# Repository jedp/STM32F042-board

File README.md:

## STM32F042 Board

Dev board for the
[STM32F042](https://www.st.com/resource/en/datasheet/stm32f042c4.pdf).

### Programming

I'm using the ST-Link on an ST Discovery board to program this.

These ST Header CN2 Pins should be connected to the corresponding pins on this
dev board:

1. Don't connect
2. CLK
3. GND
4. DIO
5. NRST

Leave pin 1 (target 3V3) unconnected. It seems to do no harm, but it won't work
if connected.

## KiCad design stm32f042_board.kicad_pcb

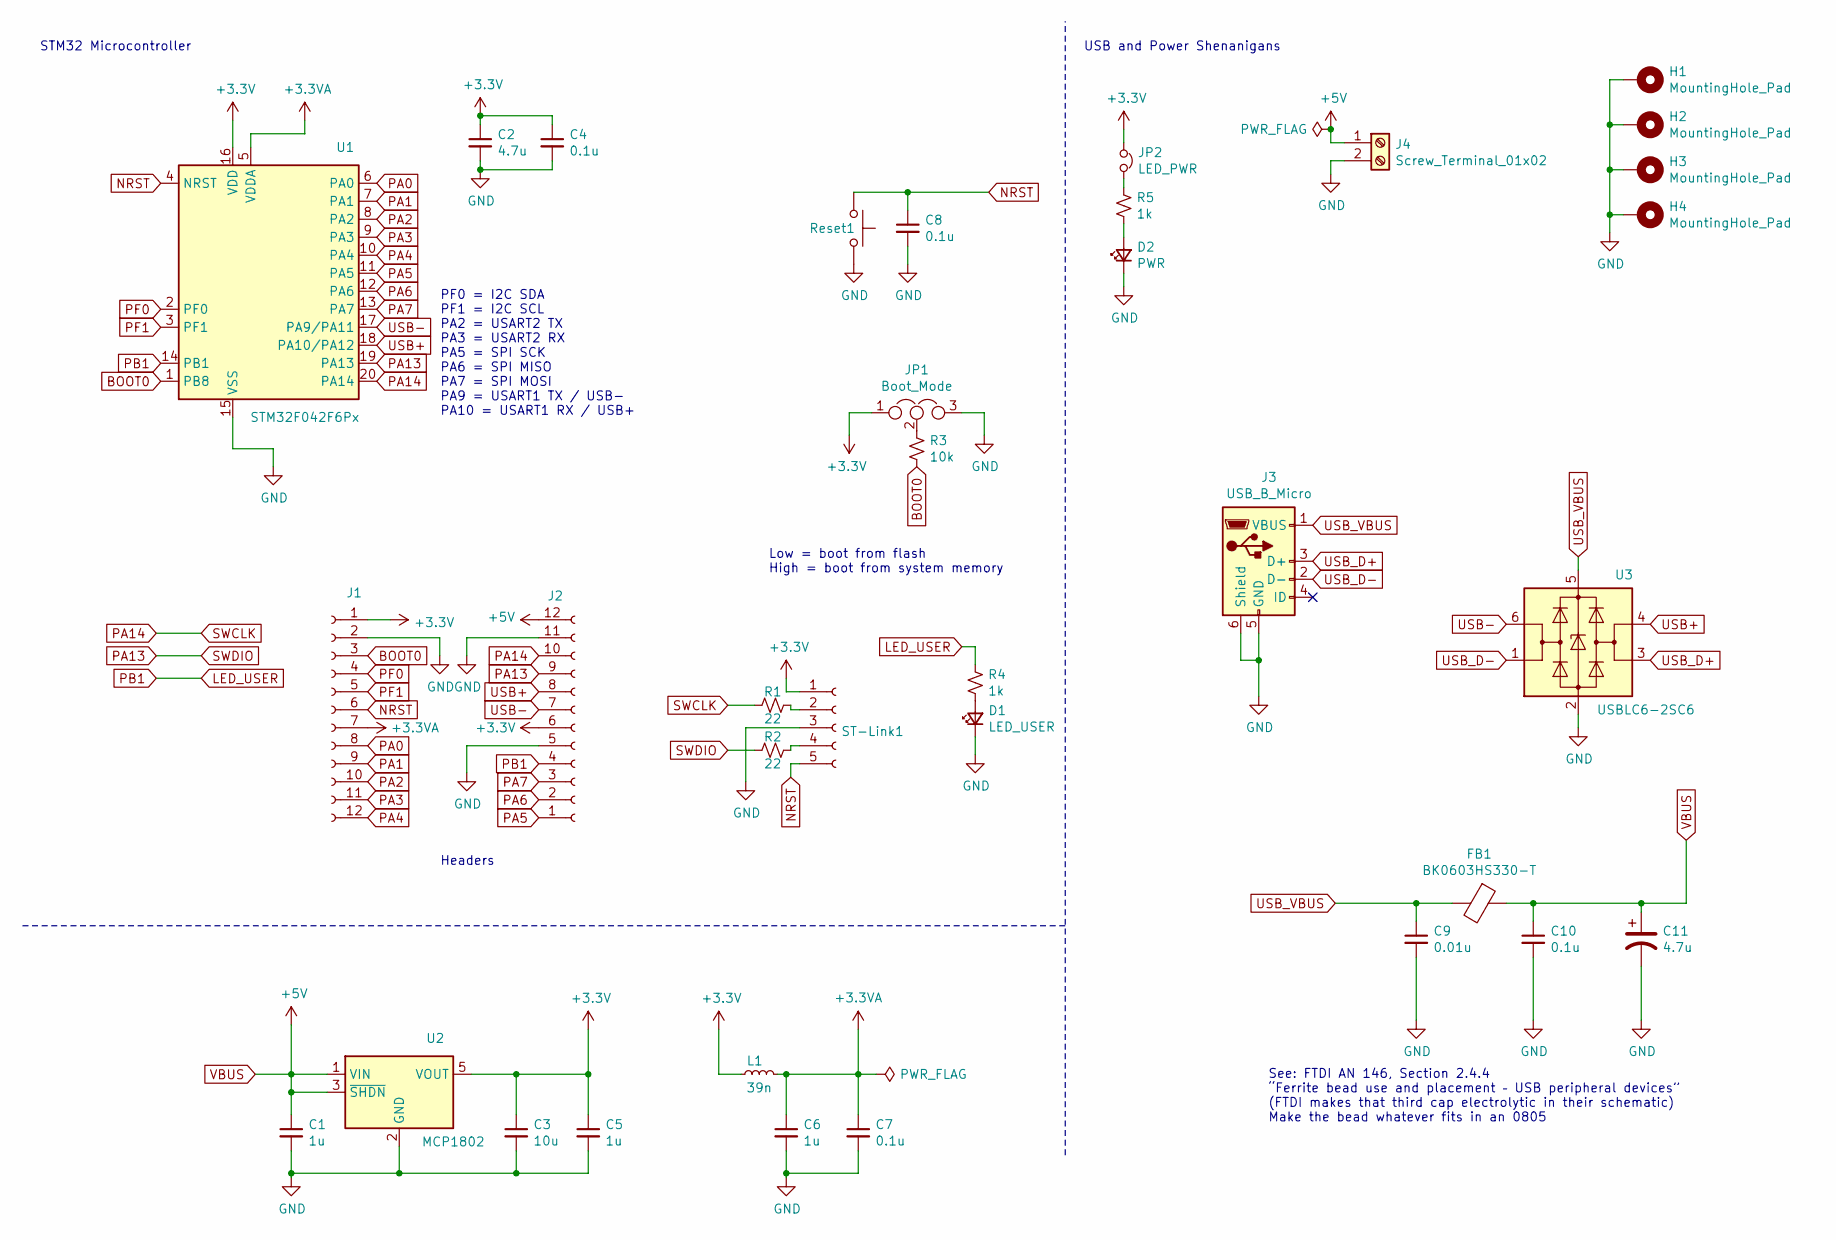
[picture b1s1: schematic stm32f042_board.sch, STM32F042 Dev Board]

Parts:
C1, C5: 1u; C_0805_2012Metric
C2: 4.7u; C_0603_1608Metric
C3: 10u; C_0805_2012Metric
C4, C7: 0.1u; C_0603_1608Metric
C6: 1u; C_0603_1608Metric
C8, C10: 0.1u; C_0805_2012Metric
C9: 0.01u; C_0805_2012Metric
C11: 4.7u; CP_Elec_4x5.4
D1: LED_USER; LED_0603_1608Metric
D2: PWR; LED_0603_1608Metric
FB1: BK0603HS330-T; L_0805_2012Metric
H1, H2, H3, H4: MountingHole_Pad; MountingHole_3.2mm_M3_ISO7380_Pad
J1, J2: Conn_01x12_Female; PinSocket_1x12_P2.54mm_Vertical
J3: USB_B_Micro; USB_Micro-B_Molex-105017-0001
J4: Screw_Terminal_01x02; TerminalBlock_MetzConnect_Type055_RT01502HDWU_1x02_P5.00mm_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
JP1: Boot_Mode; PinHeader_1x03_P2.54mm_Vertical
JP2: LED_PWR; PinHeader_1x02_P2.54mm_Vertical
L1: 39n; L_0805_2012Metric
R1, R2: 22; R_0805_2012Metric
R3: 10k; R_0603_1608Metric
R4, R5: 1k; R_0805_2012Metric
Reset1: SW_Push; SW_SPST_B3U-1000P-B
ST-Link1: Conn_01x05_Female; PinHeader_1x05_P2.54mm_Vertical
U1: STM32F042F6Px; TSSOP-20_4.4x6.5mm_P0.65mm
U2: MCP1802; SOT-23-5
U3: USBLC6-2SC6; SOT-23-6

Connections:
+3.3VA: C6.1, C7.1, J1.7, L1.2, U1.5 (VDDA)
+3V3: C2.1, C3.1, C4.1, C5.1, J1.1, J2.6, JP1.1, JP2.1, L1.1, ST-Link1.1, U1.16 (VDD), U2.5 (VOUT); also elsewhere on the board
BOOT0: J1.3, R3.2, U1.1 (PB8)
GND: C1.2, C2.2, C3.2, C4.2, C5.2, C6.2, C7.2, C8.2, C9.2, C10.2, C11.2, D1.1 (K), D2.1 (K), H1.1, H2.1, H3.1, H4.1, J1.2, J2.5, J2.11, J3.5 (GND), J3.6 (Shield), J4.2, JP1.3, Reset1.2, ST-Link1.3, U1.15 (VSS), U2.2 (GND), U3.2 (GND); also elsewhere on the board
LED_USER: J2.4, R4.1, U1.14 (PB1)
NRST: C8.1, J1.6, Reset1.1, ST-Link1.5, U1.4 (NRST); also elsewhere on the board
unnamed 6: D1.2 (A), R4.2; also elsewhere on the board
unnamed: D2.2 (A), R5.2
unnamed: JP1.2, R3.1
unnamed: JP2.2, R5.1
unnamed 11: R1.1, ST-Link1.2; also elsewhere on the board
unnamed 12: R2.1, ST-Link1.4; also elsewhere on the board
PA0: J1.8, U1.6 (PA0)
PA1: J1.9, U1.7 (PA1)
PA2: J1.10, U1.8 (PA2)
PA3: J1.11, U1.9 (PA3)
PA4: J1.12, U1.10 (PA4)
PA5: J2.1, U1.11 (PA5)
PA6: J2.2, U1.12 (PA6)
PA7: J2.3, U1.13 (PA7)
PA13: J2.9, R2.2, U1.19 (PA13)
PA14: J2.10, R1.2, U1.20 (PA14)
PF0: J1.4, U1.2 (PF0)
PF1: J1.5, U1.3 (PF1)
USB+: J2.8, U1.18 (PA10/PA12), U3.4 (I/O2)
USB-: J2.7, U1.17 (PA9/PA11), U3.6 (I/O1)
USB_D+: J3.3 (D+), U3.3 (I/O2)
USB_D-: J3.2 (D-), U3.1 (I/O1)
USB_VBUS: C9.1, FB1.2, J3.1 (VBUS), U3.5 (VBUS)
VBUS: C1.1, C10.1, C11.1, FB1.1, J2.12, J4.1, U2.1 (VIN), U2.3 (~SHDN)

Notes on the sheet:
Low = boot from flash High = boot from system memory
See: FTDI AN 146, Section 2.4.4 “Ferrite bead use and placement – USB peripheral devices” (FTDI makes that third cap electrolytic in their schematic) Make the bead whatever fits in an 0805
STM32 Microcontroller
Headers
PF0 = I2C SDA PF1 = I2C SCL PA2 = USART2 TX PA3 = USART2 RX PA5 = SPI SCK PA6 = SPI MISO PA7 = SPI MOSI PA9 = USART1 TX / USB- PA10 = USART1 RX / USB+
USB and Power Shenanigans

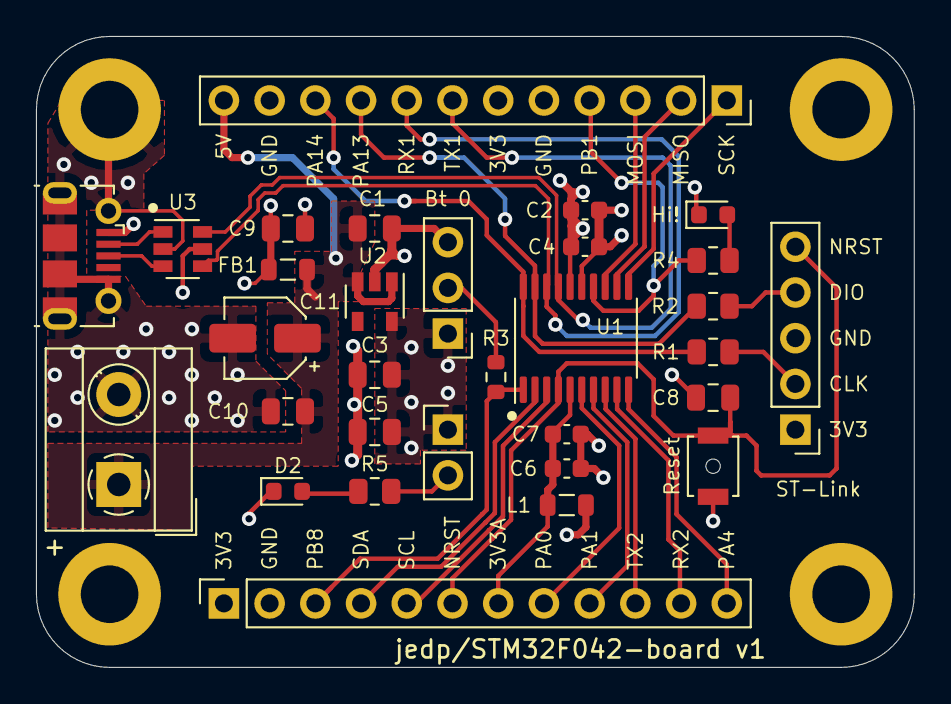
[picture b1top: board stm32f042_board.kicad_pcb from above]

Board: 4 copper layers, 48.8 x 35.1 mm, 35 parts (0 on the bottom side), 30 nets.

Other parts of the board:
Hi!: LED_USER; LED_0603_1608Metric
ST-Link: Conn_01x05_Female; PinHeader_1x05_P2.54mm_Vertical

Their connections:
+3V3: ST-Link.1; also elsewhere on the board
GND: Hi!.1, ST-Link.3; also elsewhere on the board
NRST: ST-Link.5; also elsewhere on the board
unnamed 6: Hi!.2; also elsewhere on the board
unnamed 11: ST-Link.2; also elsewhere on the board
unnamed 12: ST-Link.4; also elsewhere on the board

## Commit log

2020-11-28 STM32F042 dev board
2020-12-13 Programming notes
